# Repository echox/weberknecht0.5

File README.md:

Weberknecht 0.5

Is a servo based quadruped robot with long legs. Since spiders have 8 legs, its only 1/2 Weberknecht (daddy longlegs), therefore the name.

Required libraries:
- NewPing: https://bitbucket.org/teckel12/arduino-new-ping/wiki/Home
- Adafruit BLE Library: https://learn.adafruit.com/adafruit-feather-32u4-bluefruit-le/installing-ble-library
- Adafruit PWM servo library: https://learn.adafruit.com/16-channel-pwm-servo-driver/using-the-adafruit-library
- How to install libraries: https://learn.adafruit.com/adafruit-all-about-arduino-libraries-install-use/how-to-install-a-library

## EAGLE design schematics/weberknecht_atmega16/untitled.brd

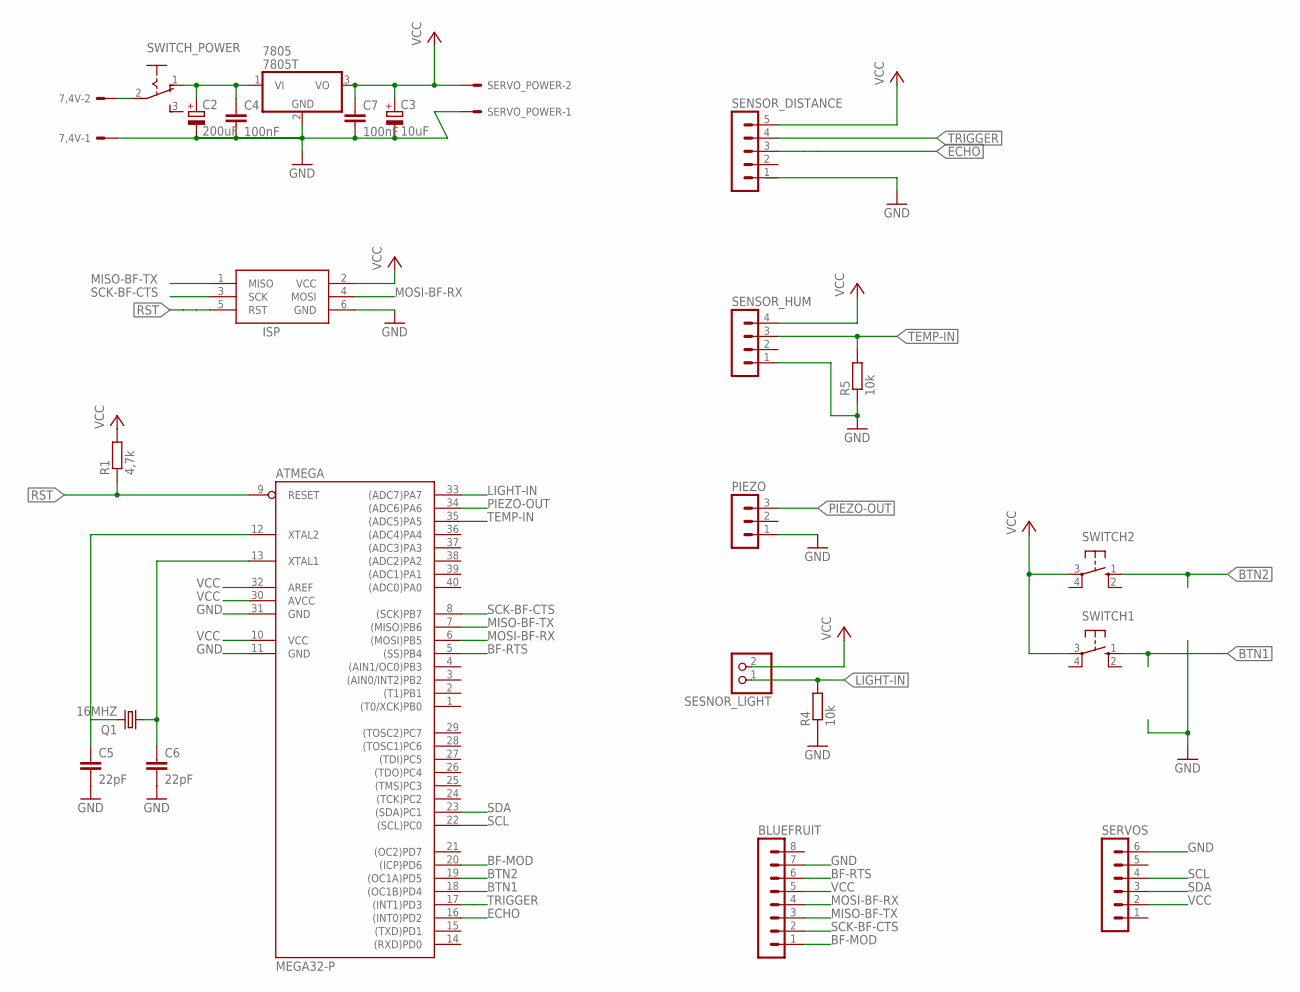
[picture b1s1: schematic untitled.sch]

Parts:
7,4V: KK-156-2
7805: 7805T; TO220H
ATMEGA: MEGA32-P; DIL40
BLUEFRUIT: MA08-1
C2: 200uF; E5-10,5
C3: 10uF; E5-10,5
C4, C7: 100nF; C025-025X050
C5, C6: 22pF; C025-025X050
ISP: AVRISP-6; AVRISP
PIEZO: MA03-1
Q1: 16MHZ; HC49/S
R1: 4,7k; 0207/10
R4, R5: 10k; 0207/10
SENSOR_DISTANCE: MA05-1
SENSOR_HUM: MA04-1
SERVOS: MA06-1
SERVO_POWER: KK-156-2
SESNOR_LIGHT: PINHD-1X2; 1X02
SWITCH1, SWITCH2: 10-XX; B3F-10XX
SWITCH_POWER: 255SB

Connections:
BF-MOD: ATMEGA.20 ((ICP)PD6), BLUEFRUIT.1
BF-RTS: ATMEGA.5 ((SS)PB4), BLUEFRUIT.6
BTN1: ATMEGA.18 ((OC1B)PD4), SWITCH1.1 (S)
BTN2: ATMEGA.19 ((OC1A)PD5), SWITCH2.1 (S)
ECHO: ATMEGA.16 ((INT0)PD2), SENSOR_DISTANCE.3
GND: 7,4V.1, 7805.2 (GND), ATMEGA.11 (GND), ATMEGA.31 (GND), BLUEFRUIT.7, C2.-, C3.-, C4.2, C5.2, C6.2, C7.2, ISP.6 (GND), PIEZO.1, R4.1, R5.1, SENSOR_HUM.1, SERVOS.6, SERVO_POWER.1
LIGHT-IN: ATMEGA.33 ((ADC7)PA7), R4.2, SESNOR_LIGHT.1
MISO-BF-TX: ATMEGA.7 ((MISO)PB6), BLUEFRUIT.3, ISP.1 (MISO)
MOSI-BF-RX: ATMEGA.6 ((MOSI)PB5), BLUEFRUIT.4, ISP.4 (MOSI)
unnamed: 7,4V.2, SWITCH_POWER.2
unnamed: ATMEGA.12 (XTAL2), C5.1, Q1.2
unnamed: ATMEGA.13 (XTAL1), C6.1, Q1.1
PIEZO-OUT: ATMEGA.34 ((ADC6)PA6), PIEZO.3
RST: ATMEGA.9 (RESET), ISP.5 (RST), R1.1
SCK-BF-CTS: ATMEGA.8 ((SCK)PB7), BLUEFRUIT.2, ISP.3 (SCK)
SCL: ATMEGA.22 ((SCL)PC0), SERVOS.4
SDA: ATMEGA.23 ((SDA)PC1), SERVOS.3
TEMP-IN: ATMEGA.35 ((ADC5)PA5), R5.2, SENSOR_HUM.3
TRIGGER: ATMEGA.17 ((INT1)PD3), SENSOR_DISTANCE.4
VCC: 7805.3 (VO), ATMEGA.10 (VCC), ATMEGA.30 (AVCC), ATMEGA.32 (AREF), BLUEFRUIT.5, C3.+, C7.1, ISP.2 (VCC), R1.2, SENSOR_DISTANCE.5, SENSOR_HUM.4, SERVOS.2, SERVO_POWER.2, SESNOR_LIGHT.2, SWITCH1.3, SWITCH2.3
VIN: 7805.1 (VI), C2.+, C4.1, SWITCH_POWER.1 (O)

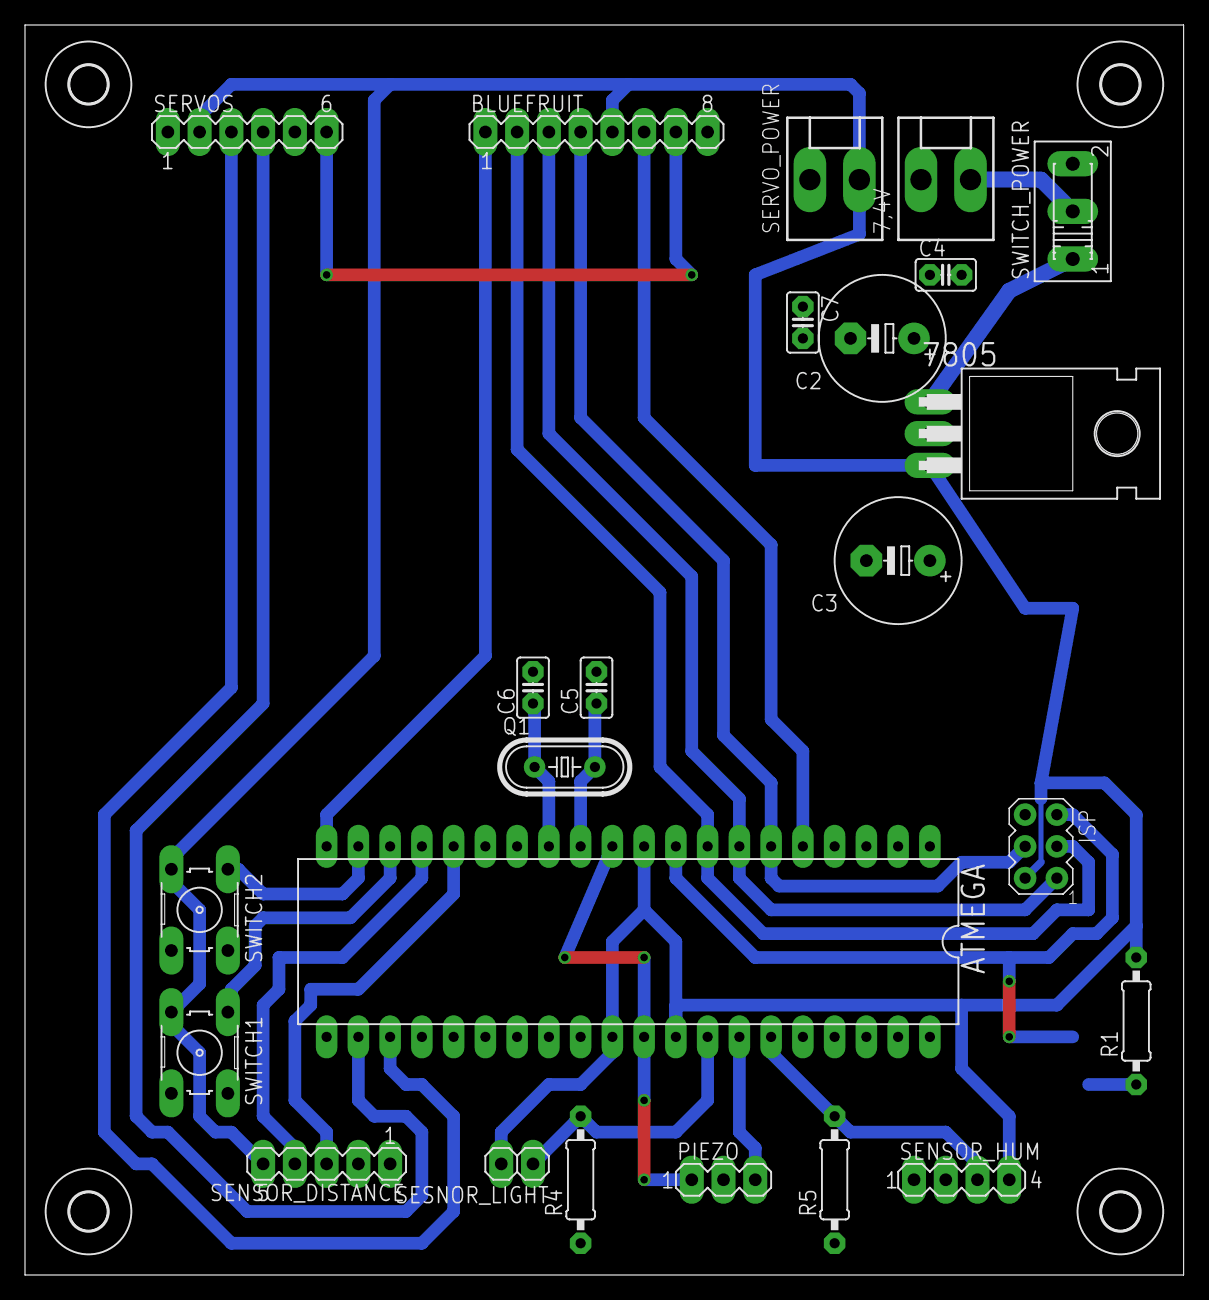
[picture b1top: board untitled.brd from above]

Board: 2 copper layers, 92.7 x 100.0 mm, 28 parts (0 on the bottom side), 21 nets.

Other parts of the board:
U$1, U$2, U$3, U$4: 3,0

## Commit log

2016-05-16 init
2016-05-16 minor fix for servo arm spacing
2016-07-07 mega commit :D
2016-07-07 Added: - resetLegs command added - ultrasounf sweep added - constants for several internal values - minor fixes
2016-07-08 - removed setServos from the main loop.
2016-07-08 - added command p to set all leg pitches with one command
2016-07-08 - added a function to set a leg's pitch and yaw with one command
2016-07-09 - final attempt to sing "Mary had a little lamb"
